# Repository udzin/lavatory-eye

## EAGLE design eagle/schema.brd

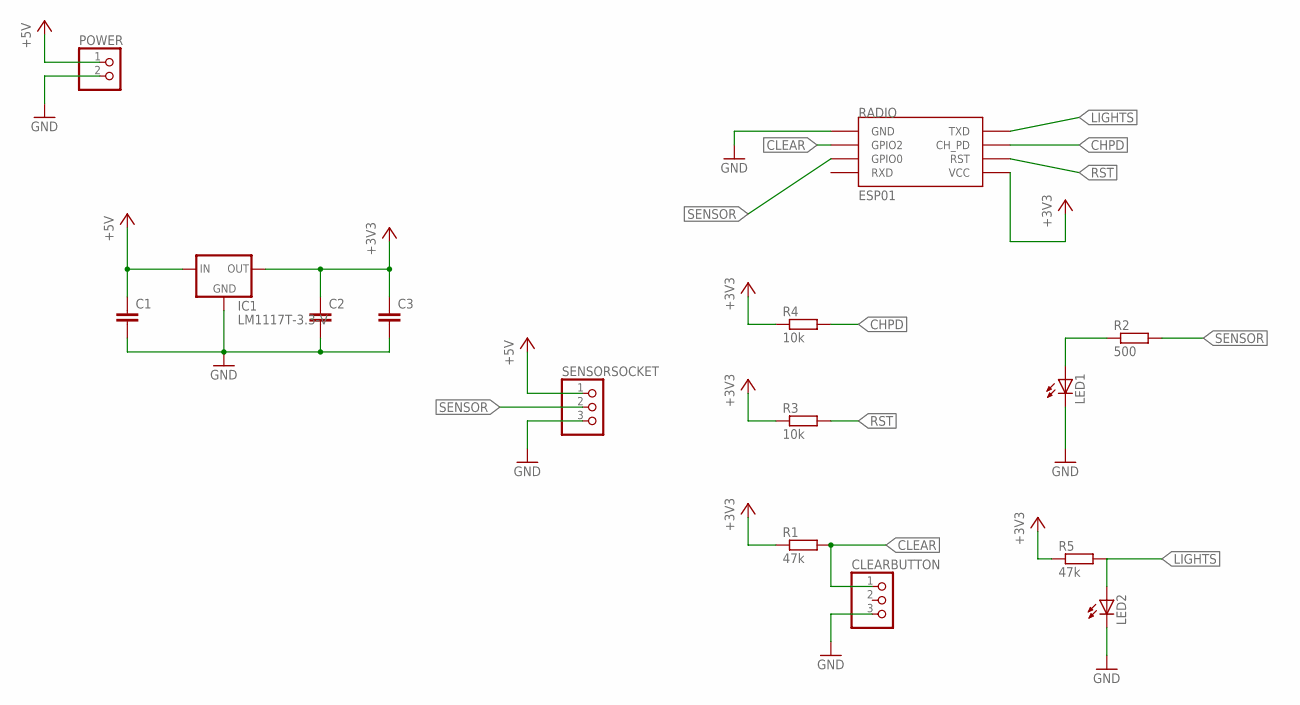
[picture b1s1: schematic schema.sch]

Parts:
C1, C2, C3: C-EU025-024X044; C025-024X044
CLEARBUTTON: PINHD-1X3; 1X03
IC1: LM1117T-3.3-V; TO220V
LED1, LED2: LED3MM
POWER: PINHD-1X2; 1X02
R1, R5: 47k; 0204/5
R2: 500; 0204/5
R3, R4: 10k; 0204/5
RADIO: ESP01
SENSORSOCKET: PINHD-1X3; 1X03

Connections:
+3V3: C2.1, C3.1, IC1.2 (OUT), R1.1, R3.1, R4.1, R5.1, RADIO.VCC
+5V: C1.1, IC1.3 (IN), POWER.1, SENSORSOCKET.1
CHPD: R4.2, RADIO.CH_PD
CLEAR: CLEARBUTTON.1, R1.2, RADIO.GPIO2
GND: C1.2, C2.2, C3.2, CLEARBUTTON.3, IC1.1 (GND), LED1.K (C), LED2.K (C), POWER.2, RADIO.GND, SENSORSOCKET.3
LIGHTS: LED2.A, R5.2, RADIO.TX (TXD)
unnamed: LED1.A, R2.1
RST: R3.2, RADIO.RST
SENSOR: R2.2, RADIO.GPIO0, SENSORSOCKET.2

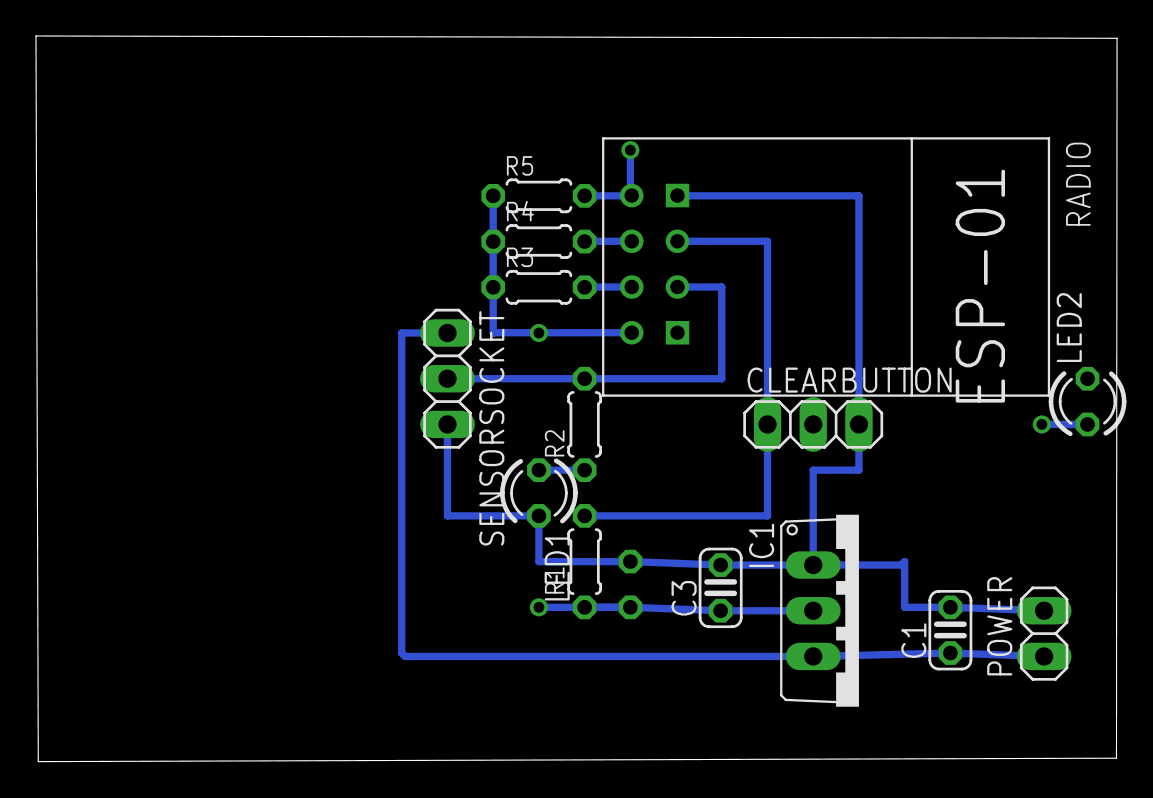
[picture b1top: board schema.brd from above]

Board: 2 copper layers, 60.1 x 40.3 mm, 15 parts (1 on the bottom side), 9 nets.

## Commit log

2016-03-28 initial
2016-03-31 client mode and new colorful page
2016-04-01 fix json format and interrupt init first
2016-05-08 added light sensor
2016-05-10 lights pin changed for well boot
2016-06-04 added static ip
2016-09-26 Added chrome extesion sources
2016-09-26 added option for enabling desktop notifications
